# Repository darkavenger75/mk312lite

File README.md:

# mk-312 lite

## Introduction

A smaller, lighter, cheaper and easier to assemble version of the mk-312 with most of its functionality

- LiFePO4 instead of Pb battery
- 90 x 120 mm single PCB design
- Most components SMT (JLCPCB will do most of the work)
- No inputs, though

## Board ordering instructions

PCB
- Default settings by JLCPCB work fine. Feel free to choose different color, etc. Lead-free recommended for the sake of the environment.

Front panel
- 1.2 mm aluminium, black or white. 

Assembly
- Economic, Bottom side, as many PCBs as you wish. "Confirm Parts Placement" recommended. 
- Automatic selection of parts after uploading BOM and CPL worked well, but better check for errors. 
- Check part placement and rotation, esp. ATmega, transistors and 5V DC/DC converter (K7805).  

## Parts ordering information

You will in addition require all pin-through-hole parts, they are included in the BOM (V4), though. Do not forget the buttom covers and knobs for the potentiometers. 
In addition, you will have to order
- A 12V 2Ah LiFePo4 4-cell battery with BMS and connector matching the one you used on the board. I got mine from Eremit in Germany. You can use a 3-cell LiPo battery pack instead (there is a LDO voltage regulator on the 9V rail), but the R5/R6 voltage divider must be adjusted to avoid incorrect low battery warning/shutdown.
- A matching external CHARGER for your battery pack with 5.5/2.1 mm connector, center positive. Do NOT just connect a power supply without current limiter.   

## Board assembly Instructions

- The two transformers, battery connector and polyfuse (if not SMT) go to the bottom of the PCB (or the front panel will not fit).
- Best shorten the spindels of the pots beforehand, if you bought the 20 mm version. Also shorten/remove the taps.  
- The connectors and LEDs are best soldered with the front panel attached such that they fit neatly into the respective holes. 
- Ensure polarity of your battery pack and charger is correct, or things may get fried. 

## Firmware

The firmware has not been modified, for instructions see the "firmware" folder. 

## Case

The front panel goes directly on top of the PCB. Use washers on the pots to level the front panel as required.  
Bottom closes with plain aluminum panel.  
A simple 3D printed case - two halves which close by 4 pins or headless screws - can be found in the "case" directory.

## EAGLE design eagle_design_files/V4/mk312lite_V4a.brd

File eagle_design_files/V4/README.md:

Minor update because some parts are no longer available at JLCPCB
- IRLL2705 replaced by ZXMN4A06GTA (or NDT3055L)
- K7805MT-500R4 replaced by TPSM365R6V5 (V4) or LM2674 (V4a)
- Polyfuse replaced by SMD version

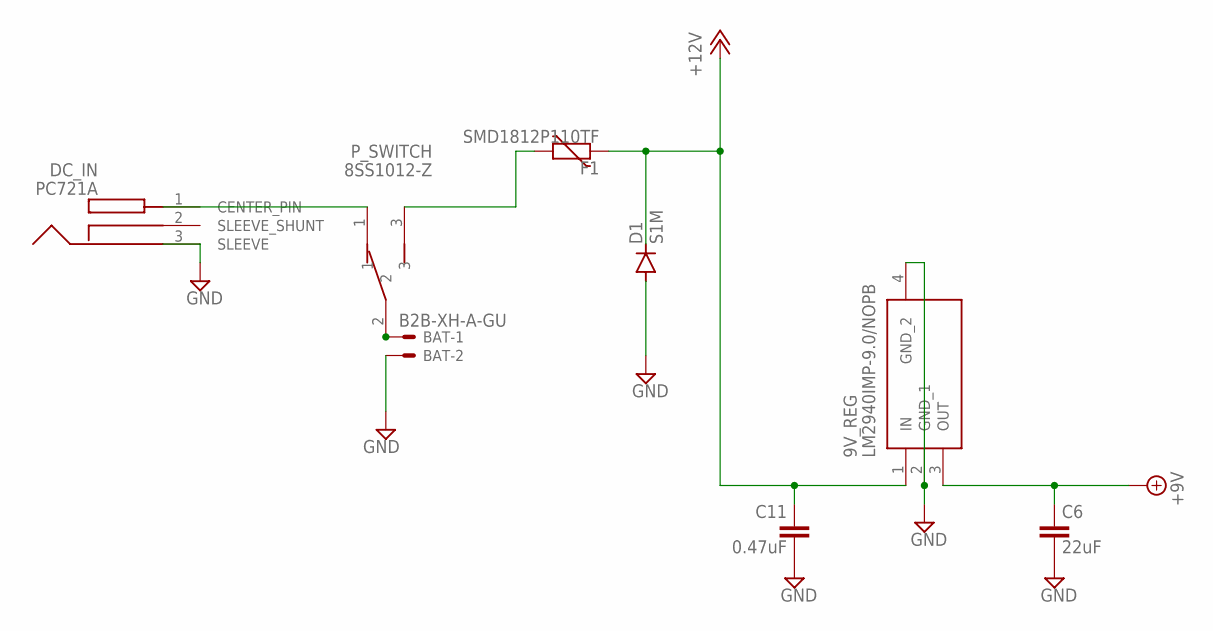
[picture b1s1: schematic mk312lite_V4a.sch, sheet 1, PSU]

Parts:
9V_REG: LM2940IMP-9.0/NOPB; SOT230P700X180-4N
BAT: B2B-XH-A-GU; JST-XH-02-PACKAGE-LONG-PAD
C6: 22uF; C1206
C11: 0.47uF; C0805
D1: S1M; SMA
DC_IN: PC721A
F1: SMD1812P110TF; CT/CN1812
P_SWITCH: 8SS1012-Z; 8SS1012Z

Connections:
+9V: 9V_REG.3 (OUT), C6.1; also elsewhere on the board
+12V: 9V_REG.1 (IN), C11.1, D1.C, F1.2; also elsewhere on the board
GND: 9V_REG.2 (GND_1), 9V_REG.4 (GND_2), BAT.2, C6.2, C11.2, D1.A, DC_IN.3 (SLEEVE); also elsewhere on the board
unnamed: BAT.1, P_SWITCH.2
unnamed: F1.1, P_SWITCH.3
unnamed: DC_IN.1 (CENTER_PIN), P_SWITCH.1

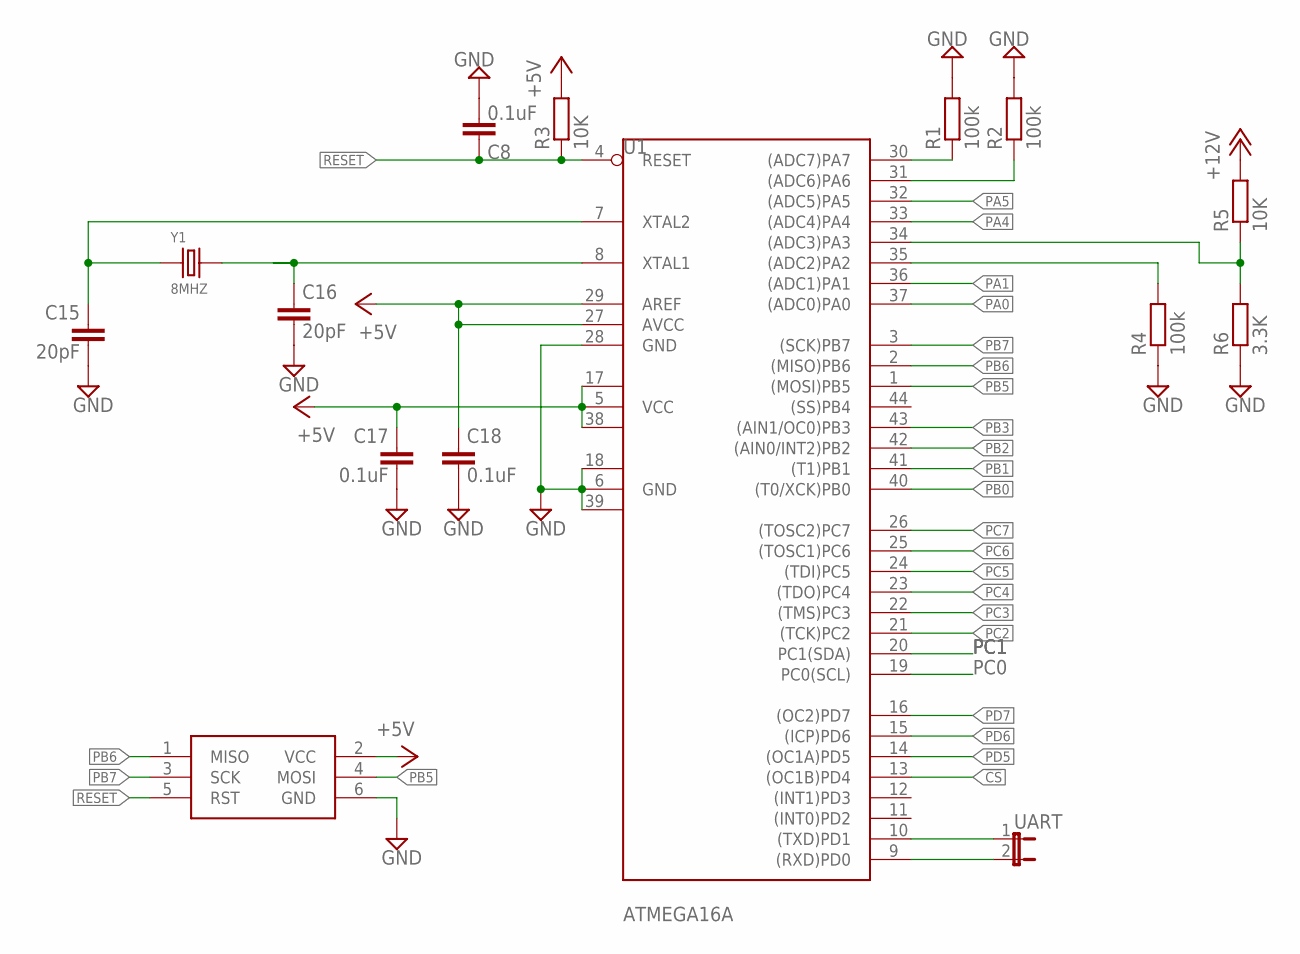
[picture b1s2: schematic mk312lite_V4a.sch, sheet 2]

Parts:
C8, C17, C18: 0.1uF; C0805
C15, C16: 20pF; C0603
ISP1: AVRISP-6; AVRISP
R1, R2, R4: 100k; R0805
R3, R5: 10K; R0805
R6: 3.3K; R0805
U1: ATMEGA16A; TQFP44
UART: JP1E; JP1
Y1: 8MHZ; X2-SMD-5.0X3.2X1.3MM

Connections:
!CS: U1.13 ((OC1B)PD4); also elsewhere on the board
+5V: C17.1, C18.1, ISP1.2 (VCC), R3.2, U1.5 (VCC), U1.17 (VCC1), U1.27 (AVCC), U1.29 (AREF), U1.38 (VCC2); also elsewhere on the board
+12V: R5.2; also elsewhere on the board
GND: C8.2, C15.2, C16.2, C17.2, C18.2, ISP1.6 (GND), R1.2, R2.2, R4.1, R6.1, U1.6 (GND), U1.18 (GND1), U1.28 (GND), U1.39 (GND2); also elsewhere on the board
unnamed: R5.1, R6.2, U1.34 ((ADC3)PA3)
unnamed: R4.2, U1.35 ((ADC2)PA2)
unnamed: R1.1, U1.30 ((ADC7)PA7)
unnamed: C16.1, U1.8 (XTAL1), Y1.2
unnamed: R2.1, U1.31 ((ADC6)PA6)
unnamed: U1.10 ((TXD)PD1), UART.1
unnamed: U1.9 ((RXD)PD0), UART.2
unnamed: C15.1, U1.7 (XTAL2), Y1.1
PA0: U1.37 ((ADC0)PA0); also elsewhere on the board
PA1: U1.36 ((ADC1)PA1); also elsewhere on the board
PA4: U1.33 ((ADC4)PA4); also elsewhere on the board
PA5: U1.32 ((ADC5)PA5); also elsewhere on the board
PB0: U1.40 ((T0/XCK)PB0); also elsewhere on the board
PB1: U1.41 ((T1)PB1); also elsewhere on the board
PB2: U1.42 ((AIN0/INT2)PB2); also elsewhere on the board
PB3: U1.43 ((AIN1/OC0)PB3); also elsewhere on the board
PB5: ISP1.4 (MOSI), U1.1 ((MOSI)PB5); also elsewhere on the board
PB6: ISP1.1 (MISO), U1.2 ((MISO)PB6)
PB7: ISP1.3 (SCK), U1.3 ((SCK)PB7); also elsewhere on the board
PC0: U1.19 (PC0(SCL)); also elsewhere on the board
PC1: U1.20 (PC1(SDA)); also elsewhere on the board
PC2: U1.21 ((TCK)PC2); also elsewhere on the board
PC3: U1.22 ((TMS)PC3); also elsewhere on the board
PC4: U1.23 ((TDO)PC4); also elsewhere on the board
PC5: U1.24 ((TDI)PC5); also elsewhere on the board
PC6: U1.25 ((TOSC1)PC6); also elsewhere on the board
PC7: U1.26 ((TOSC2)PC7); also elsewhere on the board
PD5: U1.14 ((OC1A)PD5); also elsewhere on the board
PD6: U1.15 ((ICP)PD6); also elsewhere on the board
PD7: U1.16 ((OC2)PD7); also elsewhere on the board
RESET: C8.1, ISP1.5 (RST), R3.1, U1.4 (RESET)

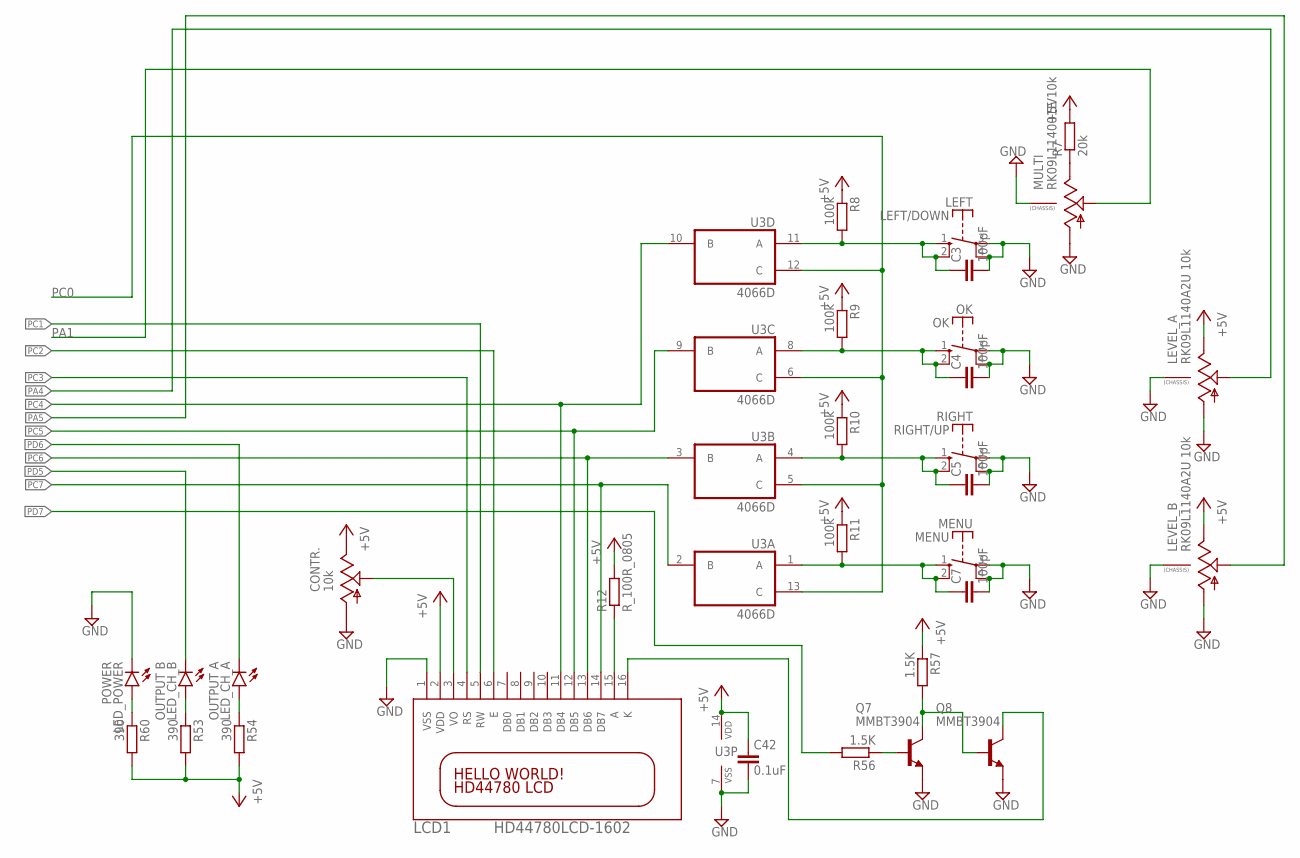
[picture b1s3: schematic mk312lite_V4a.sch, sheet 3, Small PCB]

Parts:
C3, C4, C5, C7: 100pF; C0805
C42: 0.1uF; C0805
CONTR.: 10k; B25P
LCD1: HD44780LCD-1602; LCD1602
LED_CH_A: OUTPUT A; LED3MM
LED_CH_B: OUTPUT B; LED3MM
LED_POWER: POWER; LED3MM
LEFT: LEFT/DOWN; DTE6K
LEVEL_A: RK09L1140A2U 10k; 9MM_SNAP-IN_POT
LEVEL_B: RK09L1140A2U 10k; 9MM_SNAP-IN_POT
MENU: MENU; DTE6K
MULTI: RK09L114001E 10k; 9MM_SNAP-IN_POT
OK: OK; DTE6K
Q7, Q8: MMBT3904; SOT23-BEC
R7: 20k; R0805
R8, R9, R10, R11: 100k; R0805
R12: R_100R_0805; R0805
R53, R54, R60: 390; R0805
R56, R57: 1.5K; R0805
RIGHT: RIGHT/UP; DTE6K
U3: 4066D; SO14

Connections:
+5V: C42.1, CONTR..E, LCD1.2 (VDD), LEVEL_A.3 (E), LEVEL_B.3 (E), R7.2, R8.1, R9.1, R10.1, R11.1, R12.2, R53.2, R54.2, R57.1, R60.2, U3.14 (VDD); also elsewhere on the board
GND: C3.2, C4.2, C5.2, C7.2, C42.2, CONTR..A, LCD1.1 (VSS), LED_POWER.K (C), LEFT.3, LEFT.4, LEVEL_A.1 (A), LEVEL_A.CHASSIS2, LEVEL_B.1 (A), LEVEL_B.CHASSIS2, MENU.3, MENU.4, MULTI.1 (A), MULTI.CHASSIS2, OK.3, OK.4, Q7.E, Q8.E, RIGHT.3, RIGHT.4, U3.7 (VSS); also elsewhere on the board
unnamed: MULTI.3 (E), R7.1
unnamed: C4.1, OK.1 (S), OK.2 (S), R9.2, U3.8 (A)
unnamed: C3.1, LEFT.1 (S), LEFT.2 (S), R8.2, U3.11 (A)
unnamed: C5.1, R10.2, RIGHT.1 (S), RIGHT.2 (S), U3.4 (A)
unnamed: LED_CH_B.A, R53.1
unnamed: LED_CH_A.A, R54.1
unnamed: CONTR..S, LCD1.3 (VO)
unnamed: LCD1.15 (A), R12.1
unnamed: C7.1, MENU.1 (S), MENU.2 (S), R11.2, U3.1 (A)
unnamed: LED_POWER.A, R60.1
unnamed: Q7.B, R56.1
unnamed: Q7.C, Q8.B, R57.2
unnamed: LCD1.16 (K), Q8.C
PA1: MULTI.2 (S); also elsewhere on the board
PA4: LEVEL_A.2 (S); also elsewhere on the board
PA5: LEVEL_B.2 (S); also elsewhere on the board
PC0: U3.5 (C), U3.6 (C), U3.12 (C), U3.13 (C); also elsewhere on the board
PC1: LCD1.5 (RW); also elsewhere on the board
PC2: LCD1.6 (E); also elsewhere on the board
PC3: LCD1.4 (RS); also elsewhere on the board
PC4: LCD1.11 (DB4), U3.10 (B); also elsewhere on the board
PC5: LCD1.12 (DB5), U3.9 (B); also elsewhere on the board
PC6: LCD1.13 (DB6), U3.3 (B); also elsewhere on the board
PC7: LCD1.14 (DB7), U3.2 (B); also elsewhere on the board
PD5: LED_CH_B.K (C); also elsewhere on the board
PD6: LED_CH_A.K (C); also elsewhere on the board
PD7: R56.2; also elsewhere on the board

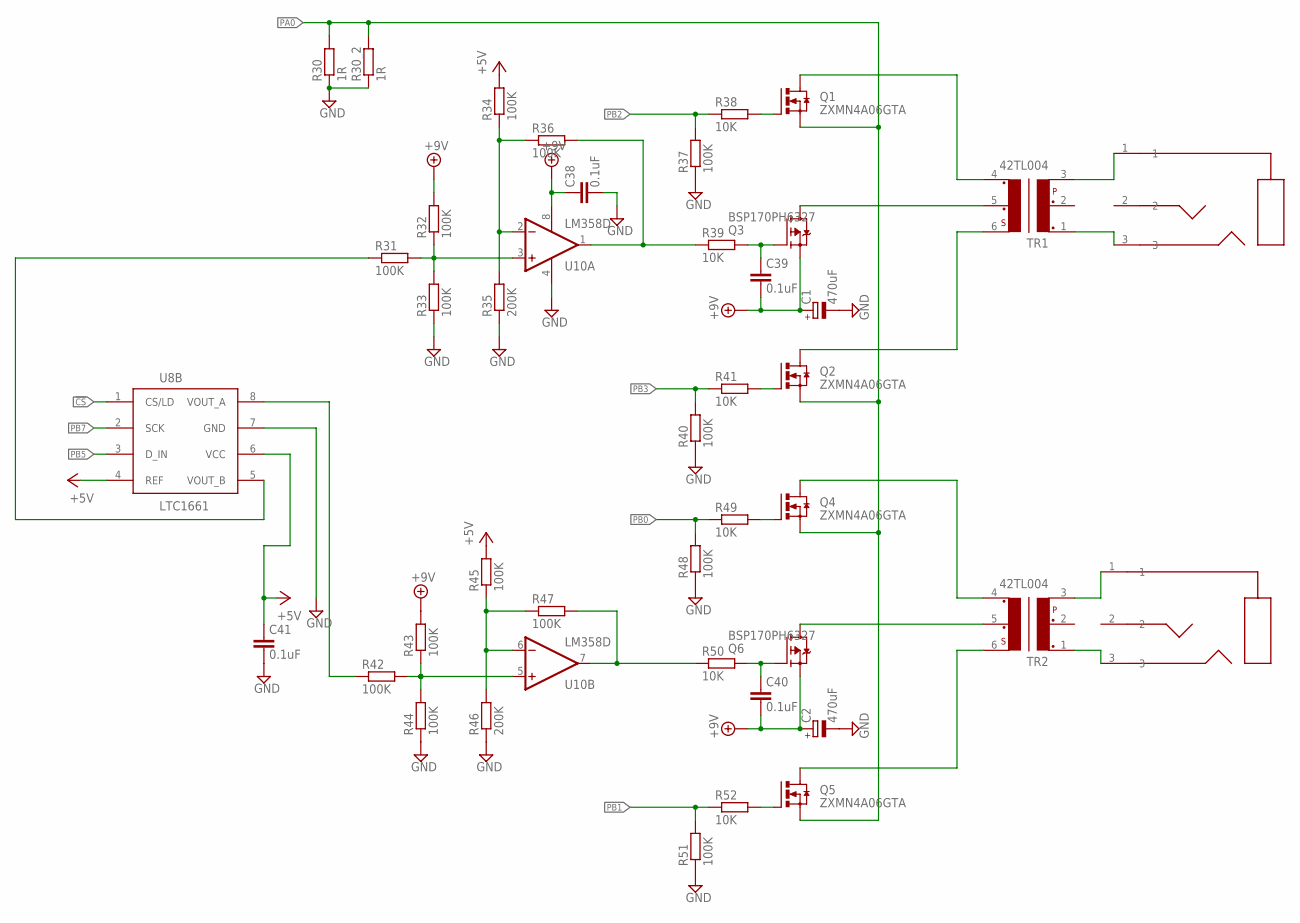
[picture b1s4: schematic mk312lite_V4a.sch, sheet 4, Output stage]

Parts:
C1, C2: 470uF; 150CLZ-1010
C38, C39, C40, C41: 0.1uF; C0805
CHAN_A: PJ-301C
CHAN_B: PJ-301C
Q1, Q2, Q4, Q5: ZXMN4A06GTA; SOT223
Q3, Q6: BSP170PH6327; SOT230P700X180-4N
R30, R30_2: 1R; R1206
R31, R32, R33, R34, R36, R37, R40, R42, R43, R44, R45, R47, R48, R51: 100K; R0805
R35, R46: 200K; R0805
R38, R39, R41, R49, R50, R52: 10K; R0805
TR1, TR2: 42TL004; 42TL
U8B: LTC1661; MSOP8
U10: LM358D; SO08

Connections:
!CS: U8B.1 (CS/LD); also elsewhere on the board
+5V: C41.1, R34.2, R45.2, U8B.4 (REF), U8B.6 (VCC); also elsewhere on the board
+9V: C1.+, C2.+, C38.1, C39.2, C40.2, Q3.3 (S), Q6.3 (S), R32.2, R43.2, U10.8 (V+); also elsewhere on the board
GND: C1.-, C2.-, C38.2, C41.2, R30.1, R30_2.1, R33.1, R35.1, R37.1, R40.1, R44.1, R46.1, R48.1, R51.1, U8B.7 (GND), U10.4 (V-); also elsewhere on the board
unnamed: Q3.2 (D), Q3.4 (D), TR1.5
unnamed: Q6.2 (D), Q6.4 (D), TR2.5
unnamed: CHAN_A.1, TR1.3
unnamed: CHAN_A.3, TR1.1
unnamed: CHAN_B.1, TR2.3
unnamed: CHAN_B.3, TR2.1
unnamed: Q1.1 (G), R38.2
unnamed: Q2.1 (G), R41.2
unnamed: C39.1, Q3.1 (G), R39.2
unnamed: R31.2, R32.1, R33.2, U10.3 (+IN)
unnamed: Q4.1 (G), R49.2
unnamed: Q5.1 (G), R52.2
unnamed: C40.1, Q6.1 (G), R50.2
unnamed: R42.2, R43.1, R44.2, U10.5 (+IN)
unnamed: Q1.2 (D), Q1.4 (D), TR1.4
unnamed: Q4.2 (D), Q4.4 (D), TR2.4
unnamed: Q5.2 (D), Q5.4 (D), TR2.6
unnamed: Q2.2 (D), Q2.4 (D), TR1.6
unnamed: R34.1, R35.2, R36.1, U10.2 (-IN)
unnamed: R45.1, R46.2, R47.1, U10.6 (-IN)
unnamed: R31.1, U8B.5 (VOUT_B)
unnamed: R42.1, U8B.8 (VOUT_A)
PA0: Q1.3 (S), Q2.3 (S), Q4.3 (S), Q5.3 (S), R30.2, R30_2.2; also elsewhere on the board
PB0: R48.2, R49.1; also elsewhere on the board
PB1: R51.2, R52.1; also elsewhere on the board
PB2: R37.2, R38.1; also elsewhere on the board
PB3: R40.2, R41.1; also elsewhere on the board
PB5: U8B.3 (D_IN); also elsewhere on the board
PB7: U8B.2 (SCK); also elsewhere on the board
PFET_A: R36.2, R39.1, U10.1 (OUT)
PFET_B: R47.2, R50.1, U10.7 (OUT)

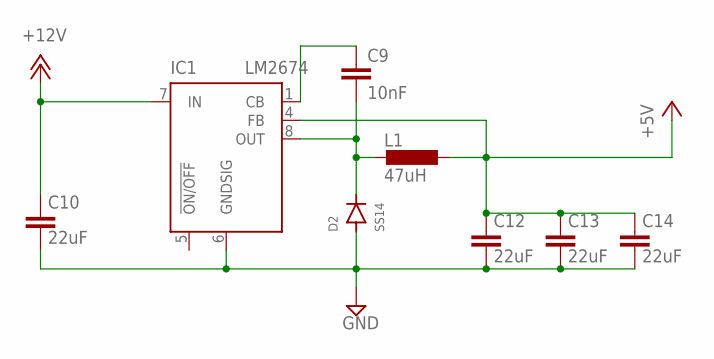
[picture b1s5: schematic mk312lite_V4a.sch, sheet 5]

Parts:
C9: 10nF; C0805
C10, C12, C13, C14: 22uF; C1206
D2: SS14; SMA
IC1: LM2674; SO08
L1: 47uH; SMNR4030-151MT

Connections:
+5V: C12.1, C13.1, C14.1, IC1.4 (FB), L1.2; also elsewhere on the board
+12V: C10.1, IC1.7 (IN); also elsewhere on the board
GND: C10.2, C12.2, C13.2, C14.2, D2.A, IC1.6 (GNDSIG); also elsewhere on the board
unnamed: C9.1, IC1.1 (CB)
unnamed: C9.2, D2.C, IC1.8 (OUT), L1.1

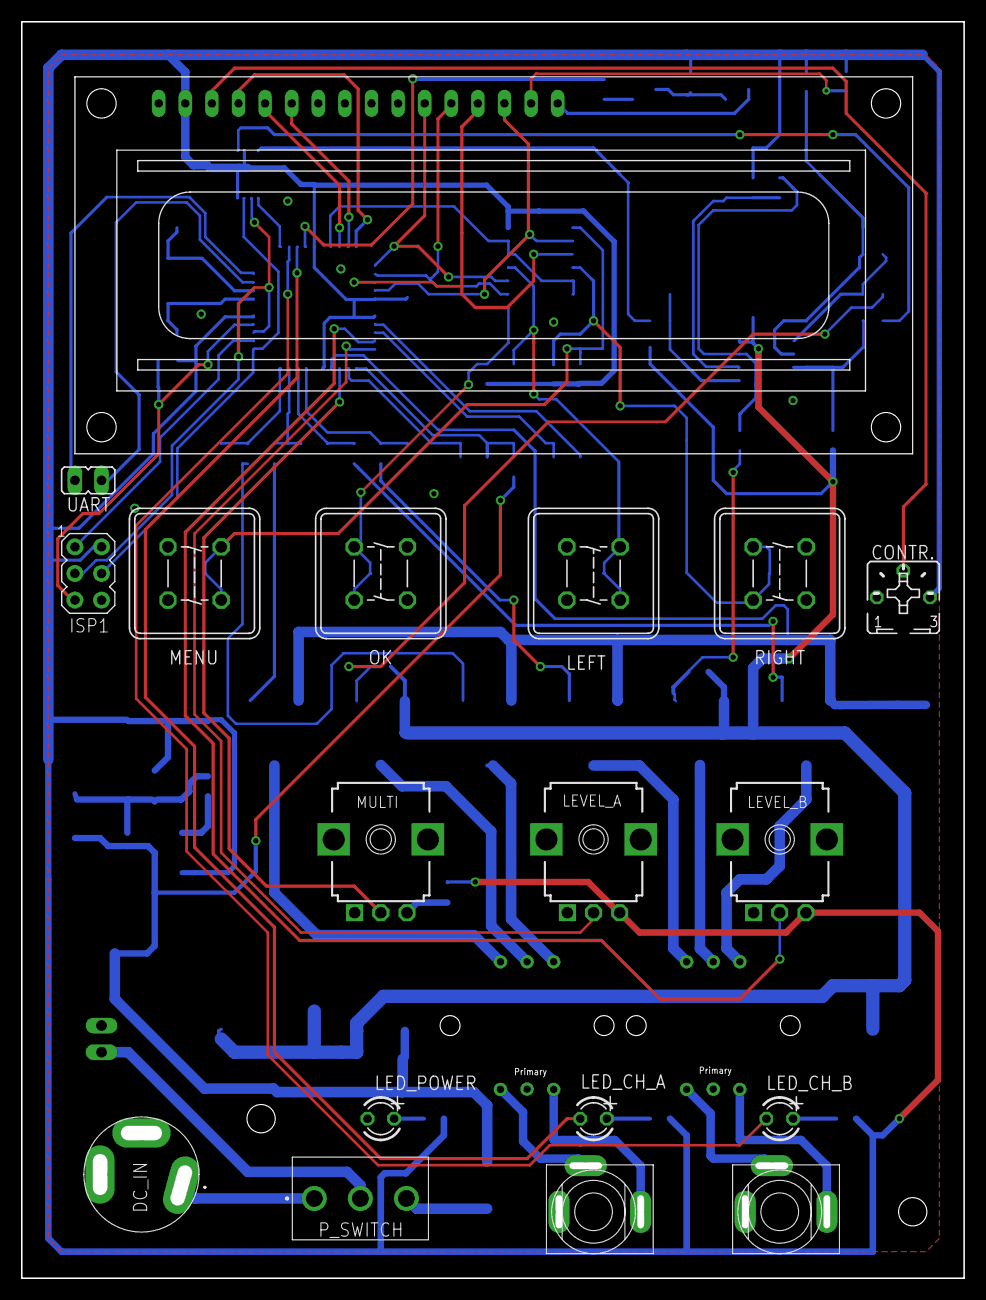
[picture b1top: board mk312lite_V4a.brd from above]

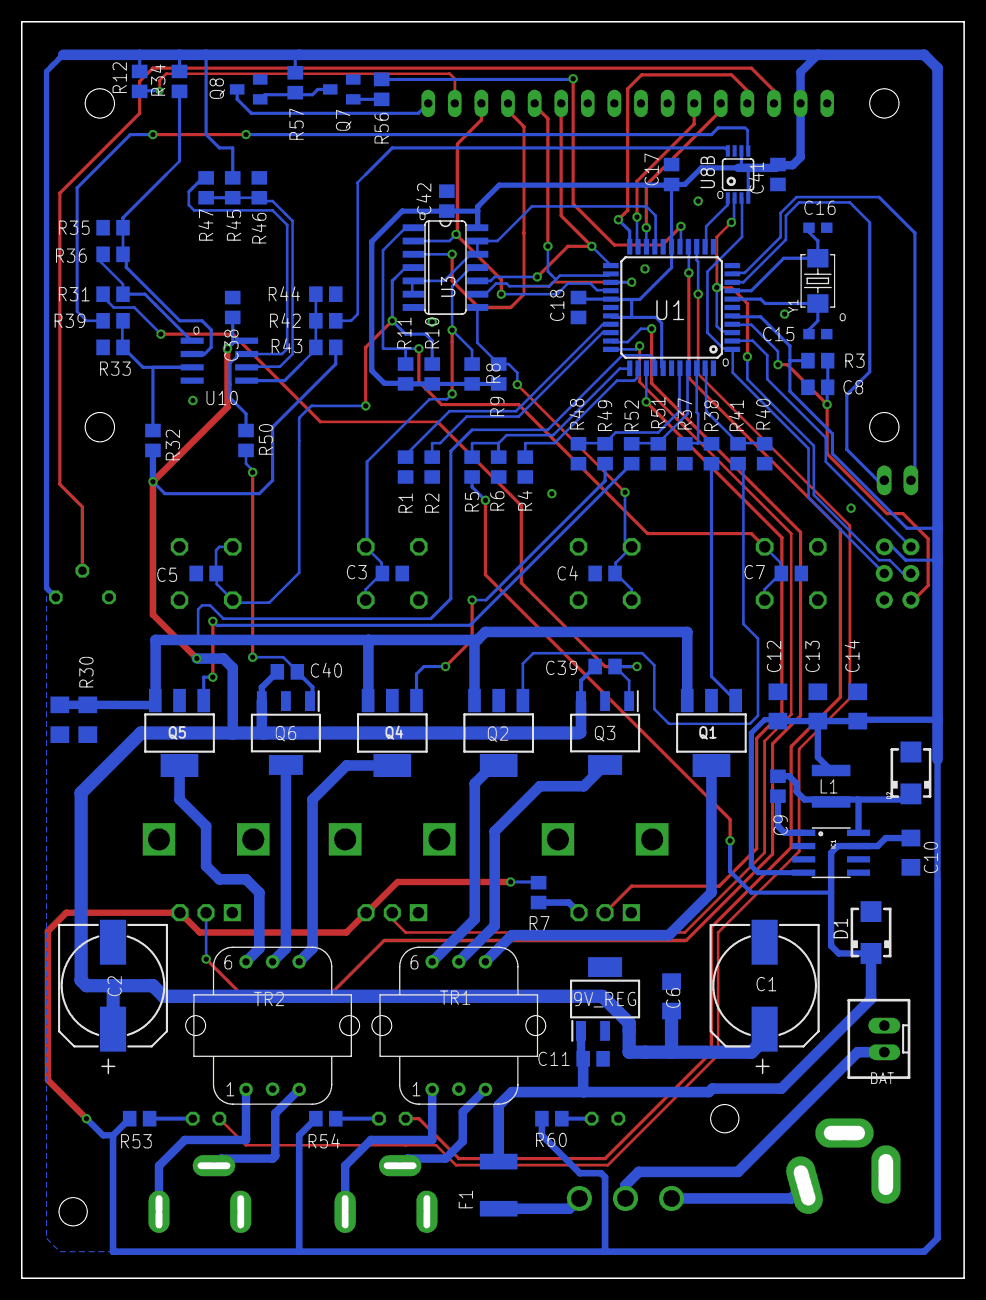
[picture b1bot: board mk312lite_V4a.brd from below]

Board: 2 copper layers, 90.0 x 120.0 mm, 104 parts (86 on the bottom side), 78 nets.

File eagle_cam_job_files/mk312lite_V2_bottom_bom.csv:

Comment,Designator,Footprint,LCSC Part #
0.1uF,C8 C17 C18 C38 C39 C40 C41 C42,C0805,
0.5R,R30,R1210,
0.47uF,C11,C0805,
1.5K,R56 R57,R0805,
3.3K,R6,R0805,
10K,R3 R5 R38 R39 R41 R49 R50 R52,R0805,
10uF,C9,C0805,
18pF,C15 C16,C0805,
20k,R7,R0805,
22uF,C6 C10,C1206,
100K,R31 R32 R33 R34 R36 R37 R40 R42 R43 R44 R45 R47 R48 R51,R0805,
100k,R1 R2 R4 R8 R9 R10 R11,R0805,
100pF,C3 C4 C5 C7,C0805,
200K,R35 R46,R0805,
390,R53 R54 R60,R0805,
470uF,C1 C2,150CLZ-1010,
4066D,U3,SO14,
ABMM2-8.000MHZ-E2-T,CRYSTAL,ABMM2,
ATMEGA16A,U1,TQFP44,
BSP170PH6327,Q3 Q6,SOT230P700X180-4N,
IRLL2705P,Q1 Q2 Q4 Q5,SOT223,
K7805MT-500R4,U$1,DFN,
LM358D,U10,SO08,
LM2940IMP-9.0/NOPB,9V_REG,SOT230P700X180-4N,
LTC1661,U8B,MSOP8,
MMBT3904 ,Q7 Q8,SOT23-BEC,
S1M,D1,SMA,

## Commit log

2023-03-01 Rename readme.md to README.md
2023-03-10 Add files via upload
    Makeshift case. Just to give an impression on how it might look like.
